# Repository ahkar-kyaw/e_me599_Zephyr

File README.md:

# Collinear mecanum drive self-balancing mobile robot

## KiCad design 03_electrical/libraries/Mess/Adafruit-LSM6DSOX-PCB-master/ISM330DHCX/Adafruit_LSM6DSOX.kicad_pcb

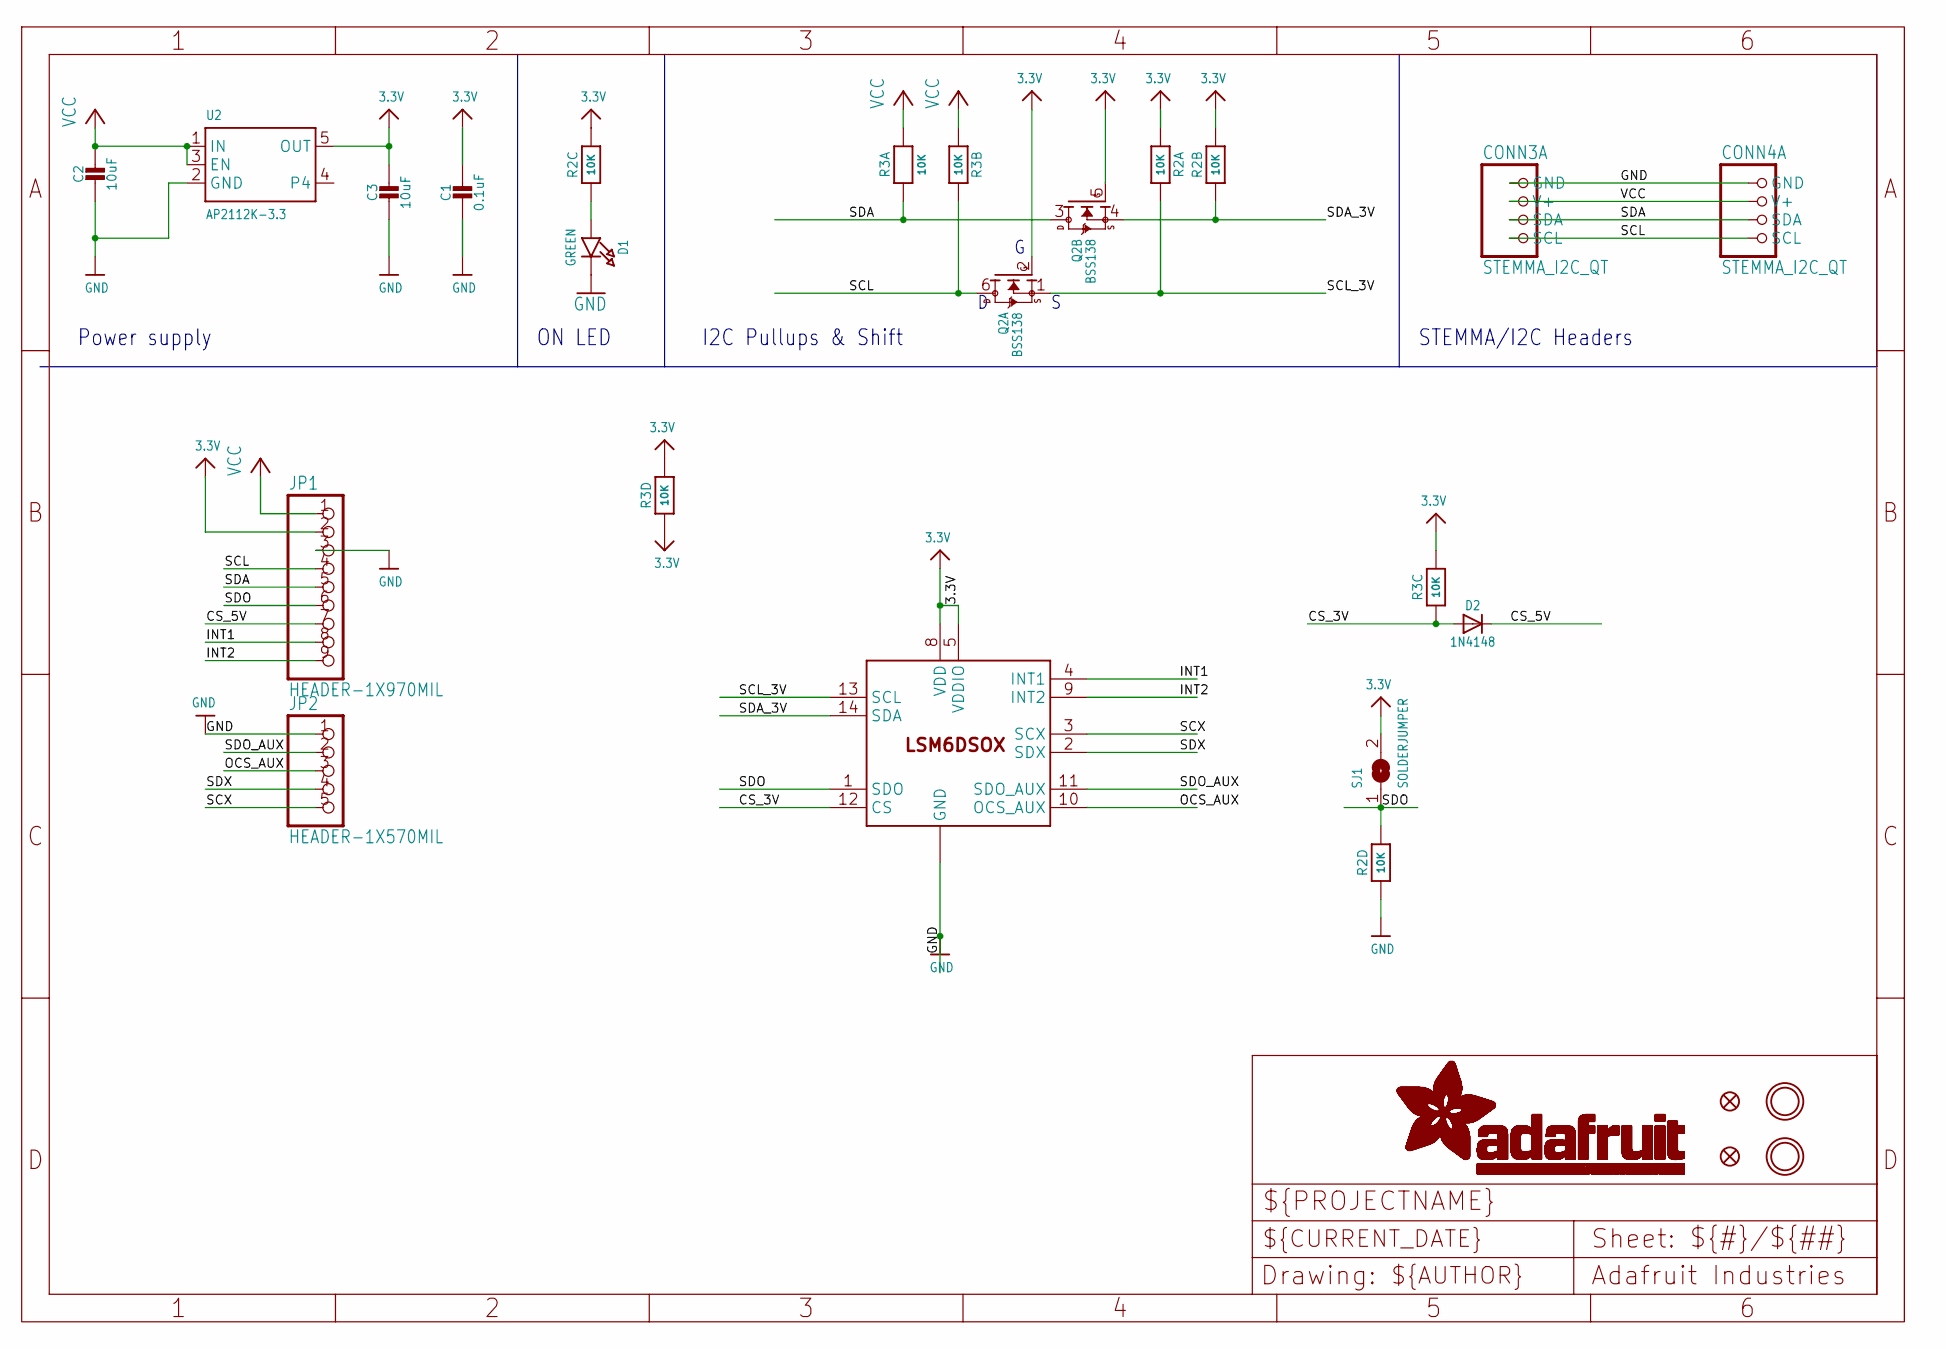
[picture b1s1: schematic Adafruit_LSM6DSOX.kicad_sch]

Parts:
C1: 0.1uF; 0603-NO
C2, C3: 10uF; 0805-NO
CONN3, CONN4: STEMMA_I2C_QT; JST_SH4
D1: GREEN; CHIPLED_0603_NOOUTLINE
D2: 1N4148; SOD-323
FID3, FID4: FIDUCIAL_1MM
JP1: HEADER-1X970MIL; 1X09_ROUND_70
JP2: HEADER-1X570MIL; 1X05_ROUND_70
Q2: BSS138; SOT363
R2, R3: 10K; RESPACK_4X0603
SJ1: SOLDERJUMPER; SOLDERJUMPER_ARROW_NOPASTE
U2: AP2112K-3.3; SOT23-5
U$1, U$17: MOUNTINGHOLE2.5; MOUNTINGHOLE_2.5_PLATED
U$2: LSM6DSOX; LGA-14L

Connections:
3.3V: C1.1, C3.1, JP1.2, Q2.2 (G), Q2.5 (G), R2.1, R2.2 (1), R2.6 (2), R3.3 (1), R3.4 (1), R3.5 (2), SJ1.2, U2.5 (OUT), U$2.5 (VDDIO), U$2.8 (VDD)
CS_3V: D2.A, R3.6 (2), U$2.12 (CS)
CS_5V: D2.C, JP1.7
GND: C1.2, C2.2, C3.2, CONN3.1 (GND), CONN4.1 (GND), D1.C, JP1.3, JP2.1, R2.4 (1), U2.2 (GND), U$2.6 (GND), U$2.7 (GND)
INT1: JP1.8, U$2.4 (INT1)
INT2: JP1.9, U$2.9 (INT2)
unnamed: D1.A, R2.3 (1)
OCS_AUX: JP2.3, U$2.10 (OCS_AUX)
SCL: CONN3.4 (SCL), CONN4.4 (SCL), JP1.4, Q2.6 (D), R3.2 (1)
SCL_3V: Q2.1 (S), R2.8 (2), U$2.13 (SCL)
SCX: JP2.5, U$2.3 (SCX)
SDA: CONN3.3 (SDA), CONN4.3 (SDA), JP1.5, Q2.3 (D), R3.1
SDA_3V: Q2.4 (S), R2.7 (2), U$2.14 (SDA)
SDO: JP1.6, R2.5 (2), SJ1.1, U$2.1 (SDO)
SDO_AUX: JP2.2, U$2.11 (SDO_AUX)
SDX: JP2.4, U$2.2 (SDX)
VCC: C2.1, CONN3.2 (V+), CONN4.2 (V+), JP1.1, R3.7 (2), R3.8 (2), U2.1 (IN), U2.3 (EN)

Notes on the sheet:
STEMMA/I2C Headers
ON LED
Power supply
I2C Pullups & Shift

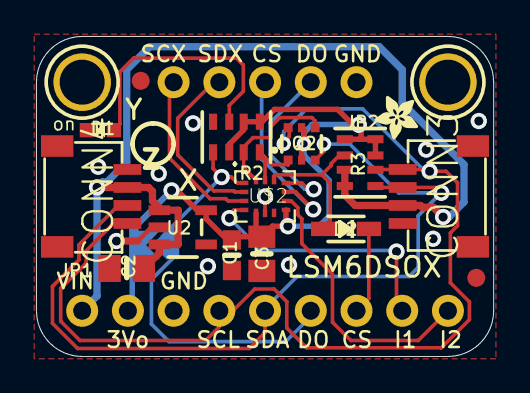
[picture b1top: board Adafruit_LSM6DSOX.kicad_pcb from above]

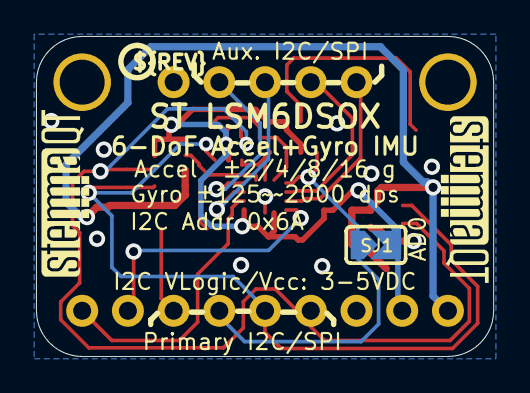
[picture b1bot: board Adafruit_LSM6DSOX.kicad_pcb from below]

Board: 2 copper layers, 25.4 x 17.8 mm, 23 parts (4 on the bottom side), 17 nets.

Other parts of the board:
U$9: ADAFRUIT_2.5MM
U$25: PCBFEAT-REV-040
U$30, U$31: STEMMAQT

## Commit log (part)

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2026-05-18 Add AK40-10 CubeMars docs; update .gitignore
    Add vendor documentation for the CubeMars AK40-10 (KV170) actuator under 99_archive: STEP CAD file, driver/setup executables, tool, manuals, firmware, 2D drawing and installation PDFs. Expand .gitign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
2026-05-19 Add zephyr.ioc STM32 MicroXplorer config
    Add MicroXplorer (.ioc) project configuration for the zephyr firmware targeting STM32H723ZGTx. Includes STM32CubeMX settings (MxCube v6.17.0) such as RCC/peripheral clock frequencies, NVIC priorities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
2026-05-19 firmware setup
2026-05-20 Restructured folder for regeneration safety
2026-05-20 Remove zephyr.zip firmware
    Delete the archived Zephyr firmware file (04_firmware/zephyr.zip) from the repository.
2026-05-20 Move zephyr files to 04_firmware and add build
    Rename/move files from 04_firmware/zephyr/... into 04_firmware/... to flatten the firmware directory structure. Affected items include Core sources/headers, Drivers (CMSIS, STM32H7xx HAL), Middleware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
2026-05-20 Remove generated build artifacts from repository
2026-06-22 V1-Reset
    USART3
    FreeRTOS
    CPU - HSE - 400MHz
    testing task_debug
2026-06-23 baseline_01_freertos_uart_hsi_400mhz
    USART3 debug UART works at 115200 using HSI PLL source.
    HSE PLL source produced UART baud mismatch or gibberish.
    HSE validation deferred to separate clock validation step.
